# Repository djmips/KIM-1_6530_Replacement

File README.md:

"# KIM-1_6530_Replacement" 

Forked from https://github.com/CorshamTech/KIM-1_6530_Replacement

Project now archived as of October 2024 at http://retro.hansotten.nl/corsham-projects-archive/kim-1-products/kim-1-6530-replacement-board/

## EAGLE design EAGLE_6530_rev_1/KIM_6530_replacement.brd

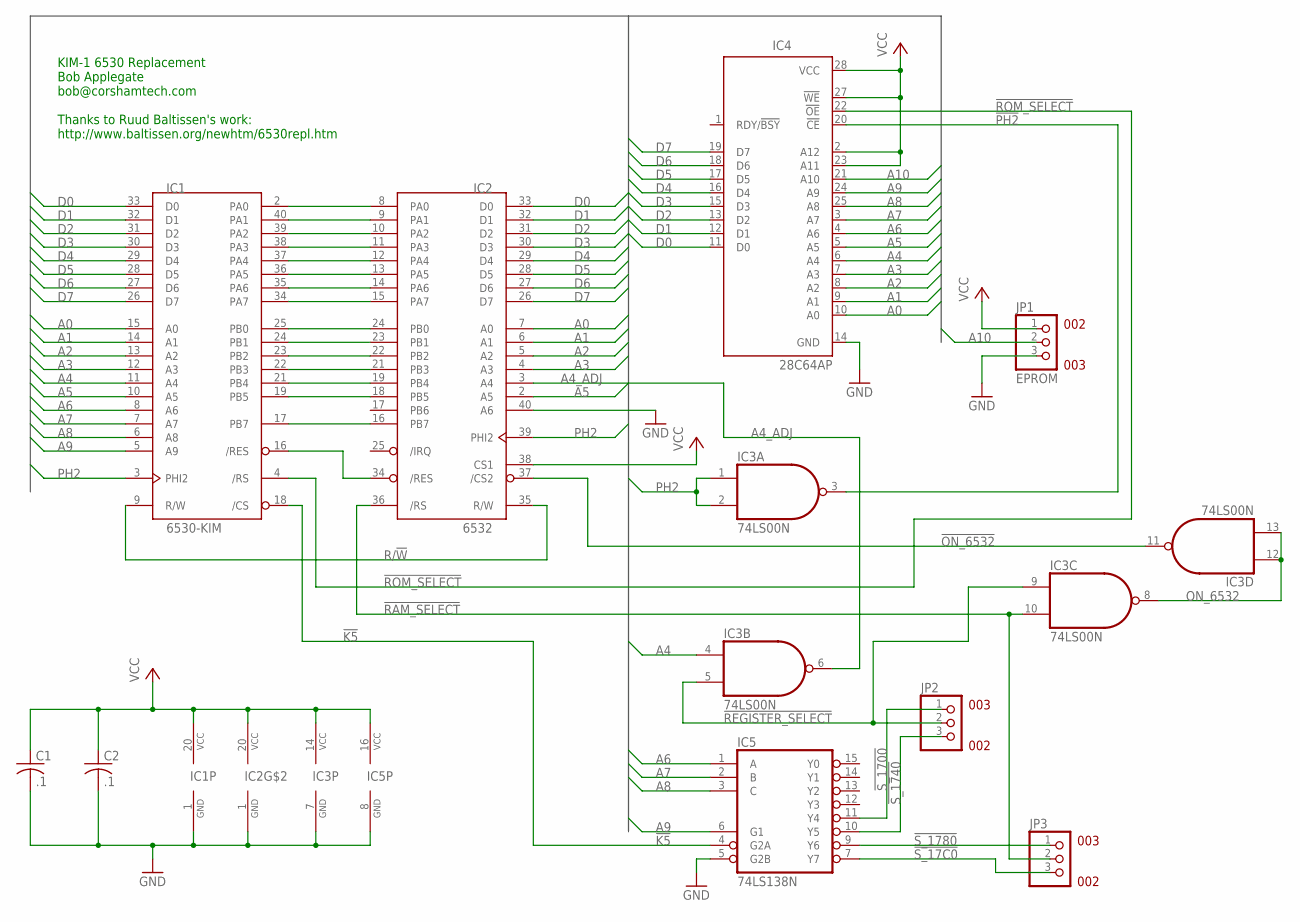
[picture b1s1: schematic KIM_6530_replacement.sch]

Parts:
C1, C2: .1; C025-025X050
IC1: 6530-KIM; DIP40
IC2: 6532; DIP40
IC3: 74LS00N; DIL14
IC4: 28C64AP; DIL28-6
IC5: 74LS138N; DIL16
JP1: EPROM; 1X03
JP2, JP3: PINHD-1X3; 1X03

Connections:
!K5: IC1.18 (/CS), IC5.4 (G2A)
!ON_6532: IC2.37 (/CS2), IC3.11 (O)
!PH2: IC3.3 (O), IC4.20 (!CE)
!RAM_SELECT: IC2.36 (/RS), IC3.10 (I1), JP3.2
!REGISTER_SELECT: IC3.5 (I1), IC3.9 (I0), JP2.2
!ROM_SELECT: IC1.4 (/RS), IC4.22 (!OE)
!S_17C0: IC5.7 (Y7), JP3.3
!S_1700: IC5.11 (Y4), JP2.1
!S_1740: IC5.10 (Y5), JP2.3
!S_1780: IC5.9 (Y6), JP3.1
A0: IC1.15 (A0), IC2.7 (A0), IC4.10 (A0)
A1: IC1.14 (A1), IC2.6 (A1), IC4.9 (A1)
A2: IC1.13 (A2), IC2.5 (A2), IC4.8 (A2)
A3: IC1.12 (A3), IC2.4 (A3), IC4.7 (A3)
A4: IC1.11 (A4), IC3.4 (I0), IC4.6 (A4)
A4_ADJ: IC2.3 (A4), IC3.6 (O)
A5: IC1.10 (A5), IC2.2 (A5), IC4.5 (A5)
A6: IC1.8 (A6), IC4.4 (A6), IC5.1 (A)
A7: IC1.7 (A7), IC4.3 (A7), IC5.2 (B)
A8: IC1.6 (A8), IC4.25 (A8), IC5.3 (C)
A9: IC1.5 (A9), IC4.24 (A9), IC5.6 (G1)
A10: IC4.21 (A10), JP1.2
D0: IC1.33 (D0), IC2.33 (D0), IC4.11 (D0)
D1: IC1.32 (D1), IC2.32 (D1), IC4.12 (D1)
D2: IC1.31 (D2), IC2.31 (D2), IC4.13 (D2)
D3: IC1.30 (D3), IC2.30 (D3), IC4.15 (D3)
D4: IC1.29 (D4), IC2.29 (D4), IC4.16 (D4)
D5: IC1.28 (D5), IC2.28 (D5), IC4.17 (D5)
D6: IC1.27 (D6), IC2.27 (D6), IC4.18 (D6)
D7: IC1.26 (D7), IC2.26 (D7), IC4.19 (D7)
GND: C1.2, C2.2, IC1.1 (GND), IC2.1 (GND), IC2.40 (A6), IC3.7 (GND), IC4.14 (GND), IC5.5 (G2B), IC5.8 (GND), JP1.3
unnamed: IC1.2 (PA0), IC2.8 (PA0)
unnamed: IC1.40 (PA1), IC2.9 (PA1)
unnamed: IC1.39 (PA2), IC2.10 (PA2)
unnamed: IC1.38 (PA3), IC2.11 (PA3)
unnamed: IC1.37 (PA4), IC2.12 (PA4)
unnamed: IC1.36 (PA5), IC2.13 (PA5)
unnamed: IC1.35 (PA6), IC2.14 (PA6)
unnamed: IC1.34 (PA7), IC2.15 (PA7)
unnamed: IC1.25 (PB0), IC2.24 (PB0)
unnamed: IC1.24 (PB1), IC2.23 (PB1)
unnamed: IC1.23 (PB2), IC2.22 (PB2)
unnamed: IC1.22 (PB3), IC2.21 (PB3)
unnamed: IC1.21 (PB4), IC2.19 (PB4)
unnamed: IC1.19 (PB5), IC2.18 (PB5)
unnamed: IC1.17 (PB7), IC2.16 (PB7)
unnamed: IC1.16 (/RES), IC2.34 (/RES)
ON_6532: IC3.8 (O), IC3.12 (I0), IC3.13 (I1)
PH2: IC1.3 (PHI2), IC2.39 (PHI2), IC3.1 (I0), IC3.2 (I1)
R/!W: IC1.9 (R/W), IC2.35 (R/W)
VCC: C1.1, C2.1, IC1.20 (VCC), IC2.20 (VCC), IC2.38 (CS1), IC3.14 (VCC), IC4.2 (A12), IC4.23 (A11), IC4.27 (!WE), IC4.28 (VCC), IC5.16 (VCC), JP1.1

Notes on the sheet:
002
003
KIM-1 6530 Replacement Bob Applegate bob@corshamtech.com Thanks to Ruud Baltissen's work: http://www.baltissen.org/newhtm/6530repl.htm

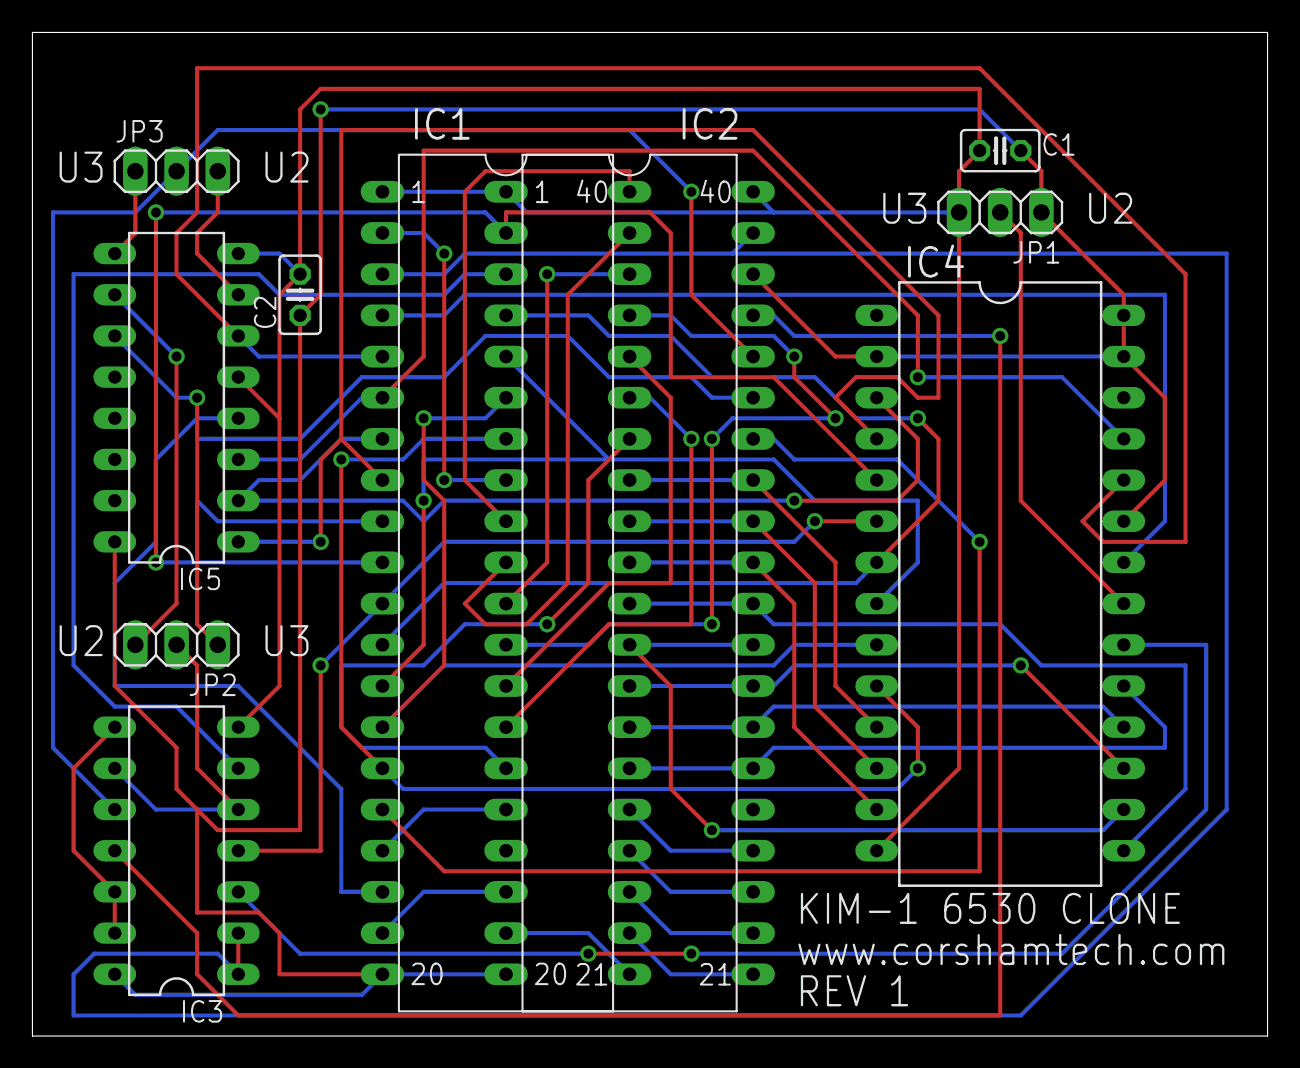
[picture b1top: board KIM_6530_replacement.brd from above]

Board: 2 copper layers, 76.2 x 61.9 mm, 10 parts (0 on the bottom side), 51 nets.

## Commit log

2024-10-03 Bob Applegate's EAGLE project.
2024-10-03 KiCad Conversion
